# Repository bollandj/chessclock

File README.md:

# chessclock

An electronic chess clock with LED 7-segment displays, based around the ATmega88PA

# Current features include:

- Basic, increment, simple delay, Bronstein delay, hourglass and count up modes

- Start time and increment, delay etc. are fully programmable

- Sound (can be enabled or disabled)

- Adjustable display brightness

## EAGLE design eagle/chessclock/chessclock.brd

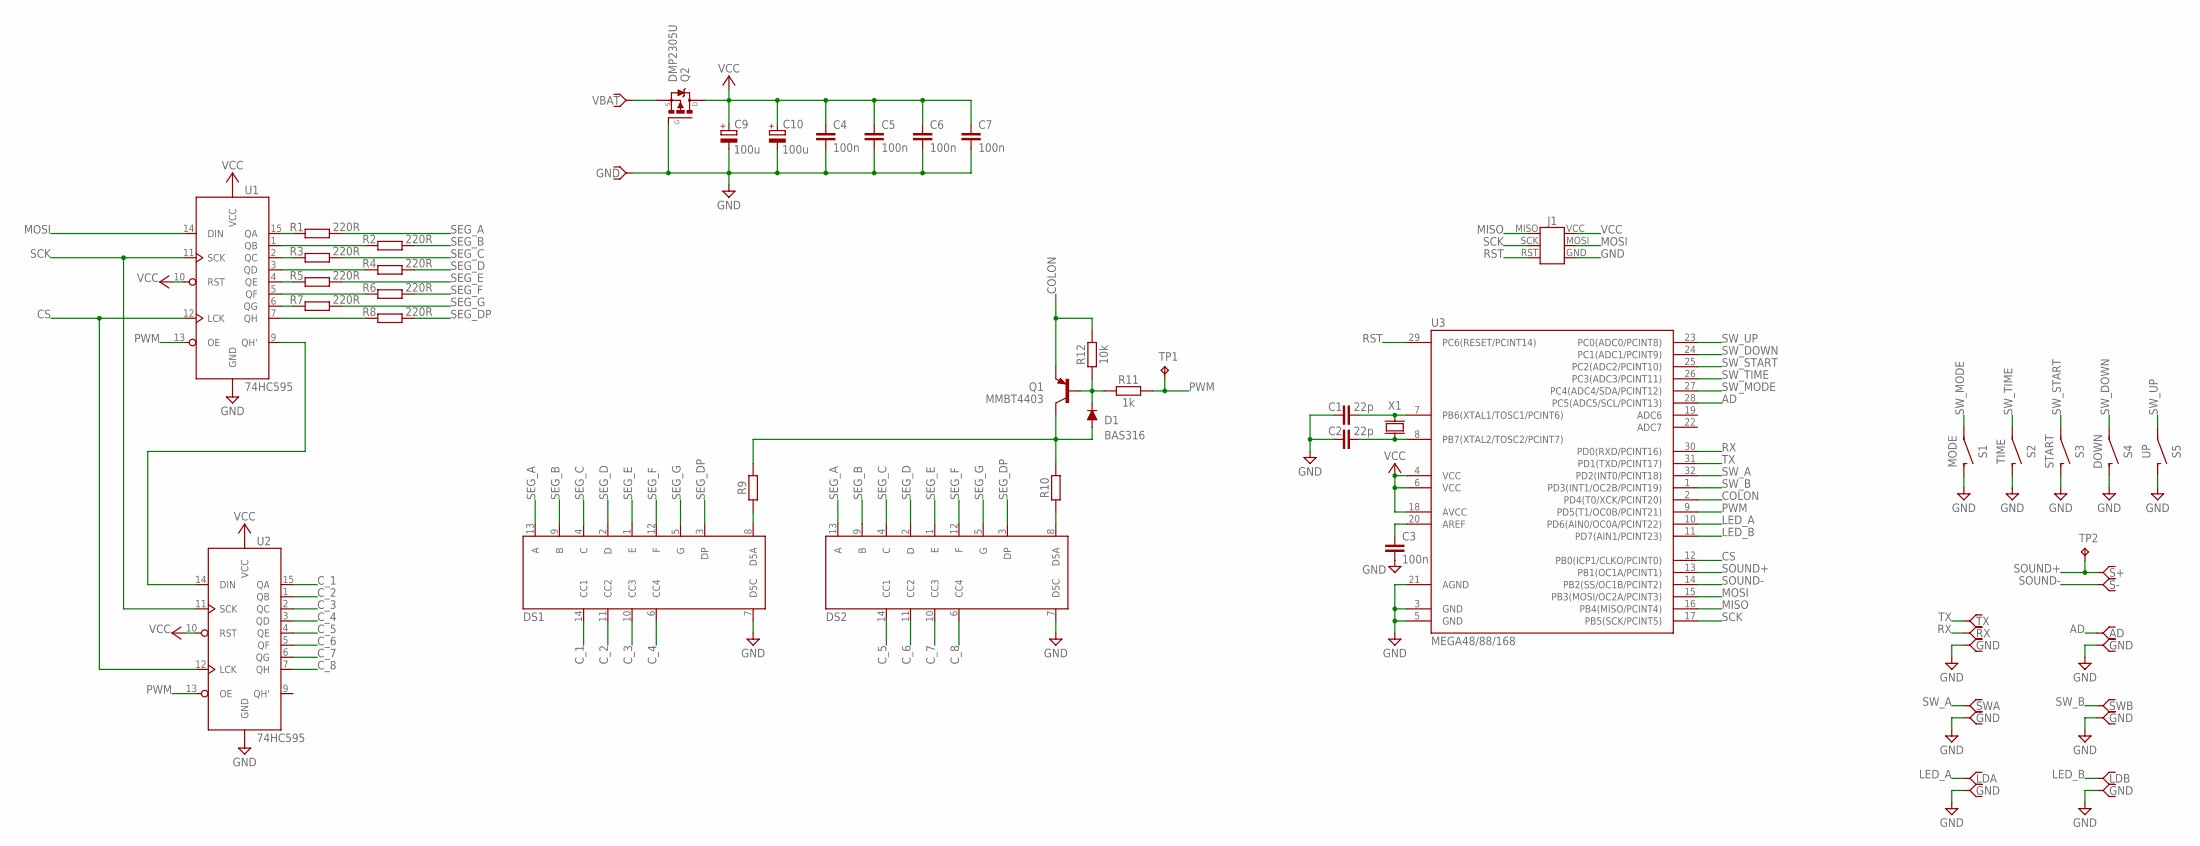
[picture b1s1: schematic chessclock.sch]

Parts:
C1, C2: 22p; C_0603
C3, C4, C5, C6, C7: 100n; C_0603
C9, C10: 100u; C_E_TH_FLAT_L_5MM
D1: BAS316; SOD323
DS1, DS2: SLR0564FR1C4BD-3.5
J1: AVRISPVERT; AVRISP
P1: SWA; CON_PIN_2MM
P2, P4, P6, P8, P9: GND; CON_PIN_2MM
P3: LDA; CON_PIN_2MM
P5: SWB; CON_PIN_2MM
P7: LDB; CON_PIN_2MM
P10: VBAT; CON_PIN_2MM
P11: S+; CON_PIN_2MM
P12: S-; CON_PIN_2MM
P13, P16: GND; CON_PIN
P14: RX; CON_PIN
P15: TX; CON_PIN
P17: AD; CON_PIN
Q1: MMBT4403; SOT23
Q2: DMP2305U; SOT23
R1, R2, R3, R4, R5, R6, R7, R8: 220R; R_0603
R9, R10: RESISTOR0603; R_0603
R11: 1k; R_0603
R12: 10k; R_0603
S1: MODE; SPST_6X6MM
S2: TIME; SPST_6X6MM
S3: START; SPST_6X6MM
S4: DOWN; SPST_6X6MM
S5: UP; SPST_6X6MM
TP1, TP2: TPTP15R; TP15R
U1, U2: 74HC595; SOIC16
U3: MEGA48/88/168; TQFP32-08
X1: XTAL_32768HZ2X6; XTAL_2X6MM

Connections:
AD: P17.1, U3.28 (PC5(ADC5/SCL/PCINT13))
COLON: Q1.2 (E), R12.2, U3.2 (PD4(T0/XCK/PCINT20))
CS: U1.12 (LCK), U2.12 (LCK), U3.12 (PB0(ICP1/CLKO/PCINT0))
C_1: DS1.14 (CC1), U2.15 (QA)
C_2: DS1.11 (CC2), U2.1 (QB)
C_3: DS1.10 (CC3), U2.2 (QC)
C_4: DS1.6 (CC4), U2.3 (QD)
C_5: DS2.14 (CC1), U2.4 (QE)
C_6: DS2.11 (CC2), U2.5 (QF)
C_7: DS2.10 (CC3), U2.6 (QG)
C_8: DS2.6 (CC4), U2.7 (QH)
GND: C1.2, C2.2, C3.1, C4.1, C5.1, C6.1, C7.1, C9.-, C10.-, DS1.7 (D5C), DS2.7 (D5C), J1.GND (6), P2.1, P4.1, P6.1, P8.1, P9.1, P13.1, P16.1, Q2.1 (G), S1.3 (2), S1.4 (2), S2.3 (2), S2.4 (2), S3.3 (2), S3.4 (2), S4.3 (2), S4.4 (2), S5.3 (2), S5.4 (2), U1.8 (GND), U2.8 (GND), U3.3 (GND), U3.5 (GND), U3.21 (AGND)
LED_A: P3.1, U3.10 (PD6(AIN0/OC0A/PCINT22))
LED_B: P7.1, U3.11 (PD7(AIN1/PCINT23))
MISO: J1.MISO (1), U3.16 (PB4(MISO/PCINT4))
MOSI: J1.MOSI (4), U1.14 (DIN), U3.15 (PB3(MOSI/OC2A/PCINT3))
unnamed: C1.1, U3.7 (PB6(XTAL1/TOSC1/PCINT6)), X1.1
unnamed: C2.1, U3.8 (PB7(XTAL2/TOSC2/PCINT7)), X1.2
unnamed: R2.1, U1.1 (QB)
unnamed: R1.1, U1.15 (QA)
unnamed: R3.1, U1.2 (QC)
unnamed: D1.A, Q1.3 (C), R9.2, R10.2
unnamed: D1.C, Q1.1 (B), R11.1, R12.1
unnamed: C3.2, U3.20 (AREF)
unnamed: R5.1, U1.4 (QE)
unnamed: R4.1, U1.3 (QD)
unnamed: R6.1, U1.5 (QF)
unnamed: R7.1, U1.6 (QG)
unnamed: R8.1, U1.7 (QH)
unnamed: U1.9 (QH'), U2.14 (DIN)
unnamed: DS2.8 (D5A), R10.1
unnamed: DS1.8 (D5A), R9.1
PWM: R11.2, TP1.TP, U1.13 (OE), U2.13 (OE), U3.9 (PD5(T1/OC0B/PCINT21))
RST: J1.RST (5), U3.29 (PC6(RESET/PCINT14))
RX: P14.1, U3.30 (PD0(RXD/PCINT16))
SCK: J1.SCK (3), U1.11 (SCK), U2.11 (SCK), U3.17 (PB5(SCK/PCINT5))
SEG_A: DS1.13 (A), DS2.13 (A), R1.2
SEG_B: DS1.9 (B), DS2.9 (B), R2.2
SEG_C: DS1.4 (C), DS2.4 (C), R3.2
SEG_D: DS1.2 (D), DS2.2 (D), R4.2
SEG_DP: DS1.3 (DP), DS2.3 (DP), R8.2
SEG_E: DS1.1 (E), DS2.1 (E), R5.2
SEG_F: DS1.12 (F), DS2.12 (F), R6.2
SEG_G: DS1.5 (G), DS2.5 (G), R7.2
SOUND+: P11.1, TP2.TP, U3.13 (PB1(OC1A/PCINT1))
SOUND-: P12.1, U3.14 (PB2(SS/OC1B/PCINT2))
SW_A: P1.1, U3.32 (PD2(INT0/PCINT18))
SW_B: P5.1, U3.1 (PD3(INT1/OC2B/PCINT19))
SW_DOWN: S4.1, S4.2 (1), U3.24 (PC1(ADC1/PCINT9))
SW_MODE: S1.1, S1.2 (1), U3.27 (PC4(ADC4/SDA/PCINT12))
SW_START: S3.1, S3.2 (1), U3.25 (PC2(ADC2/PCINT10))
SW_TIME: S2.1, S2.2 (1), U3.26 (PC3(ADC3/PCINT11))
SW_UP: S5.1, S5.2 (1), U3.23 (PC0(ADC0/PCINT8))
TX: P15.1, U3.31 (PD1(TXD/PCINT17))
VBAT: P10.1, Q2.2 (S)
VCC: C4.2, C5.2, C6.2, C7.2, C9.+, C10.+, J1.VCC (2), Q2.3 (D), U1.10 (RST), U1.16 (VCC), U2.10 (RST), U2.16 (VCC), U3.4 (VCC), U3.6 (VCC), U3.18 (AVCC)

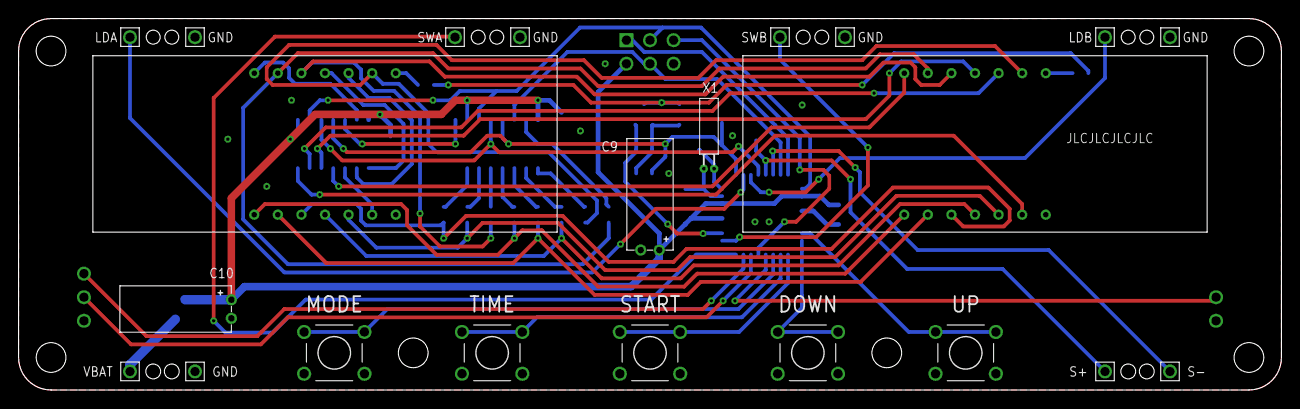
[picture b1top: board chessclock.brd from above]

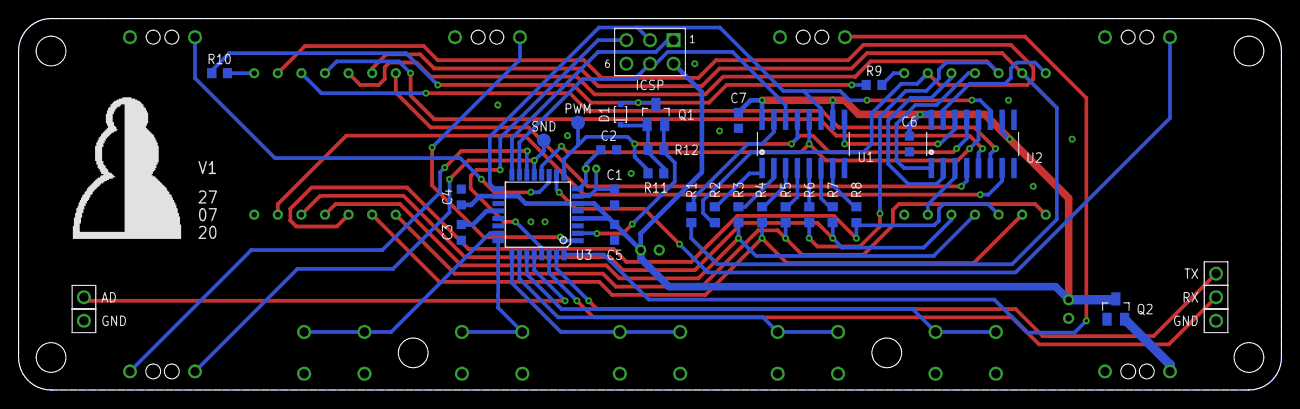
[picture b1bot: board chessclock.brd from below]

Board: 2 copper layers, 136.0 x 40.0 mm, 55 parts (33 on the bottom side), 56 nets.

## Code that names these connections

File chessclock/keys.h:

/*
 * keys.h
 *
 * Created: 04/07/2020 16:27:25
 *  Author: Joshua
 */ 


#ifndef KEYS_H_
#define KEYS_H_

#include <avr/io.h>

#define KEY_PORT PORTC
#define KEY_PIN  PINC

#define MODE_KEY  1<<PC4
#define TIME_KEY  1<<PC3
#define START_KEY 1<<PC2
#define DOWN_KEY  1<<PC1
#define UP_KEY    1<<PC0

#define KEY_MASK (MODE_KEY | TIME_KEY | START_KEY | DOWN_KEY | UP_KEY)

/* detect long presses of start/pause key */
extern uint8_t holdTimer;
extern const uint8_t holdTimerThreshold;

uint8_t keyState;
uint8_t lastKeyState;
uint8_t keyPressed;
uint8_t keyReleased;


void init_keys(void);
void scan_keys(void);


#endif /* KEYS_H_ */

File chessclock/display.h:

/*
 * display.h
 *
 * Created: 04/07/2020 13:46:35
 *  Author: Joshua
 */ 


#ifndef DISPLAY_H_
#define DISPLAY_H_

#include <avr/io.h>
#include <avr/interrupt.h>
#include <avr/pgmspace.h>

#define SPI_DDR  DDRB
#define SPI_PORT PORTB

#define SCK  PB5
#define MOSI PB3
#define SS   PB2
#define CS   PB0

inline void COLON_ON()  {PORTD |= 1<<PD4;}
inline void COLON_OFF() {PORTD &= ~(1<<PD4);}

extern uint8_t hmms;

extern volatile uint8_t displayBuffer[8];

extern volatile uint8_t blinkOsc[8];
extern volatile uint8_t blinkMask[8];

extern uint8_t blinkTimer;
extern const uint8_t blinkThreshold;

extern const uint8_t sevenSeg[38];

void init_display(uint8_t brightness);
void update_blink(void);

void write_time(uint8_t edit);
void write_char(uint8_t chr, uint8_t pos);
void write_string(const char *str, uint8_t start, uint8_t end);
void write_number_8(uint8_t num, uint8_t start);


#endif /* DISPLAY_H_ */

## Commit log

2020-07-08 Fully switched time data structure from struct to array
2020-07-11 Added basic sound and integrated display blinking with display multiplex interrupt
2020-07-11 Added time editing
2020-07-14 Added timer reset
2020-07-14 Added support for future display brightness PWM
2020-07-14 Switched to software 7-seg decoding to prepare for eventual shift register-based multiplexing
2020-07-16 Additions to settings menu
2020-07-16 Added differential piezo drive
2020-07-17 Added beep and associated sound on/off option, improved sound generation
2020-08-24 Added CAD files, shift register and colon PWM support
2020-08-24 Removed Debug folder, switched to callback-based interrupts for greater flexibility, simplified current player status tracking
2020-08-26 In progress: simple delay and Bronstein delay modes, ABC parser
2020-08-27 Added simple delay and Bronstein delay modes
2020-08-27 Added hourglass and count up modes
2020-11-13 Added .gitignore to tidy Eagle folder
2020-11-13 Removed backup files from Eagle folder
2020-11-13 Added demonstration videos
2020-11-13 Significantly reduced demo video file sizes
